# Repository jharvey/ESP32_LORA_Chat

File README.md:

# ESP32_LORA_Chat </br>
Redesign of Armachat hardware using KICAD and JLCPCB </br>
<hr />
The orginal Armachat from Peter Misenko's work at [bobricius/Armachat-circuitpython](https://github.com/bobricius/Armachat-circuitpython).</br>
This is a ESP32 with working EInk display project, which may be a useful reference https://github.com/Uspizig/EinkKeyboard</br>
 </br>
This is a redesign of bobricius/Armachat hardware to include: </br>
- ESP32 core processor </br>
- E-Ink display for lower power consumpiton </br>
- LORA communications </br>
- 18650 battery </br>
- KICAD </br>
 </br>
 
 front | back | PCB
--- | --- | ---
 |  | 
 </br>
3D model for enclosure found here </br>
https://cad.onshape.com/documents/2eca9b71ceb843e60ebed659/w/deaed59ddef0917efb45d1fe/e/0c98206fb1ddff68e078d781

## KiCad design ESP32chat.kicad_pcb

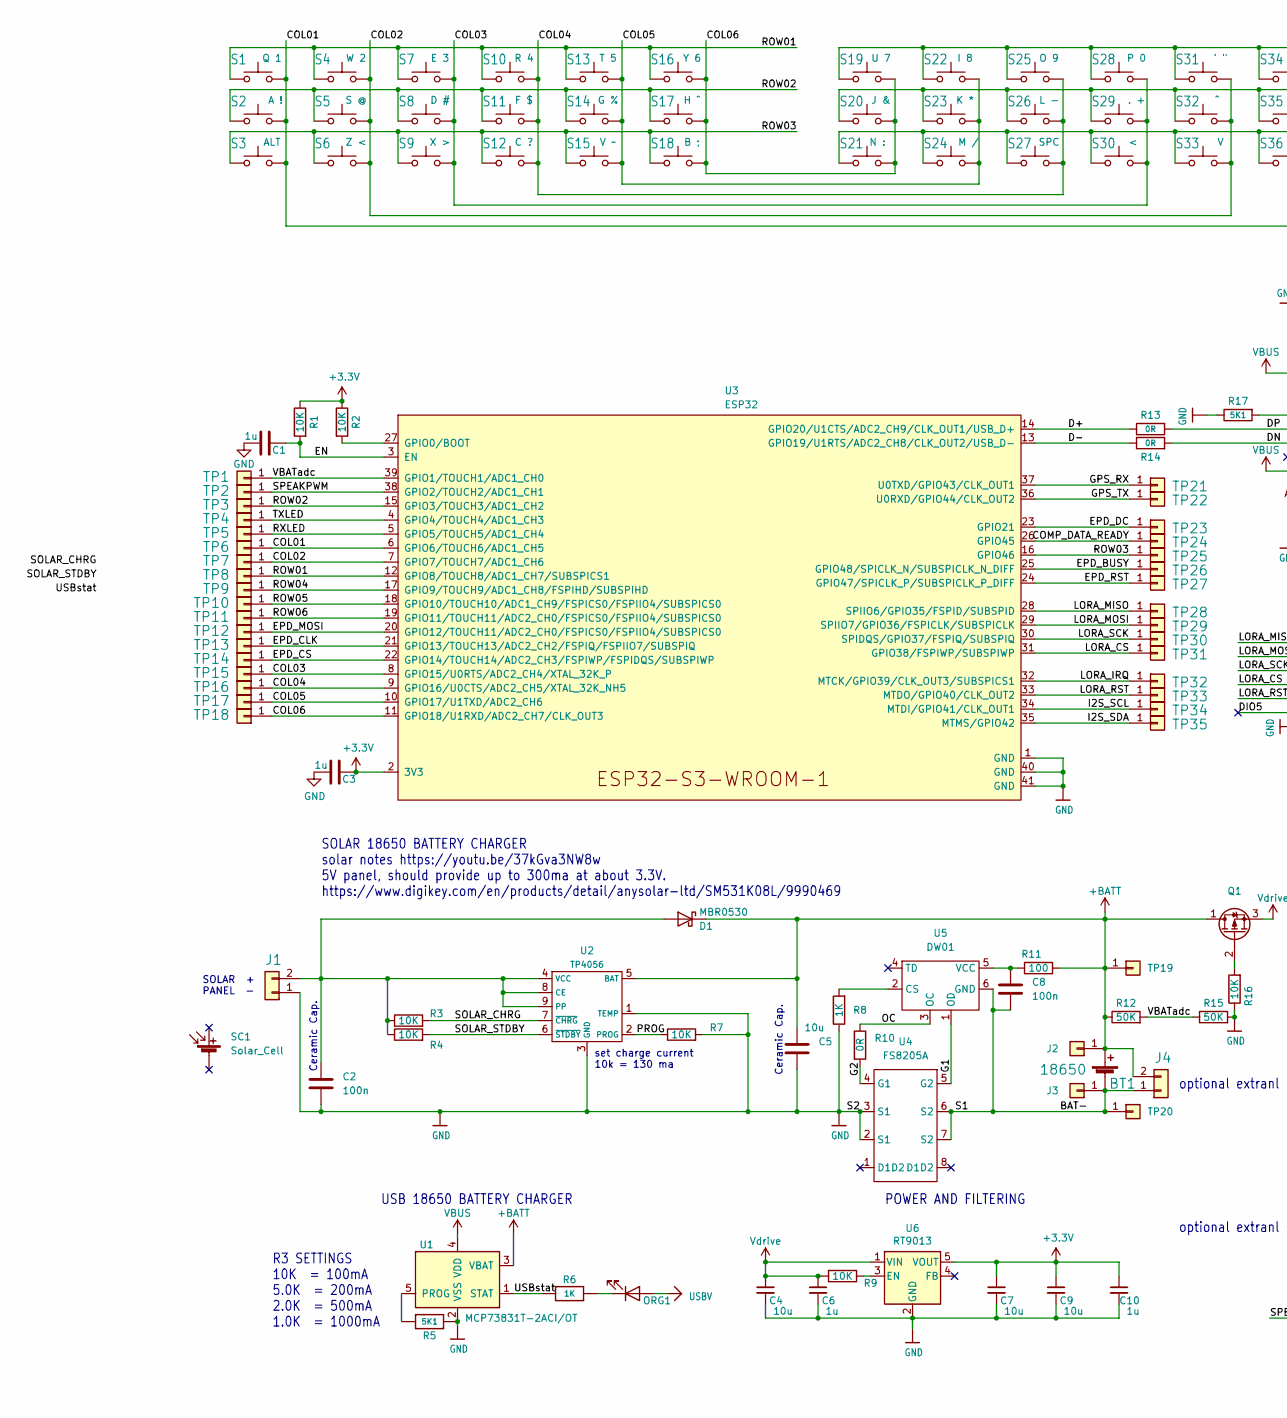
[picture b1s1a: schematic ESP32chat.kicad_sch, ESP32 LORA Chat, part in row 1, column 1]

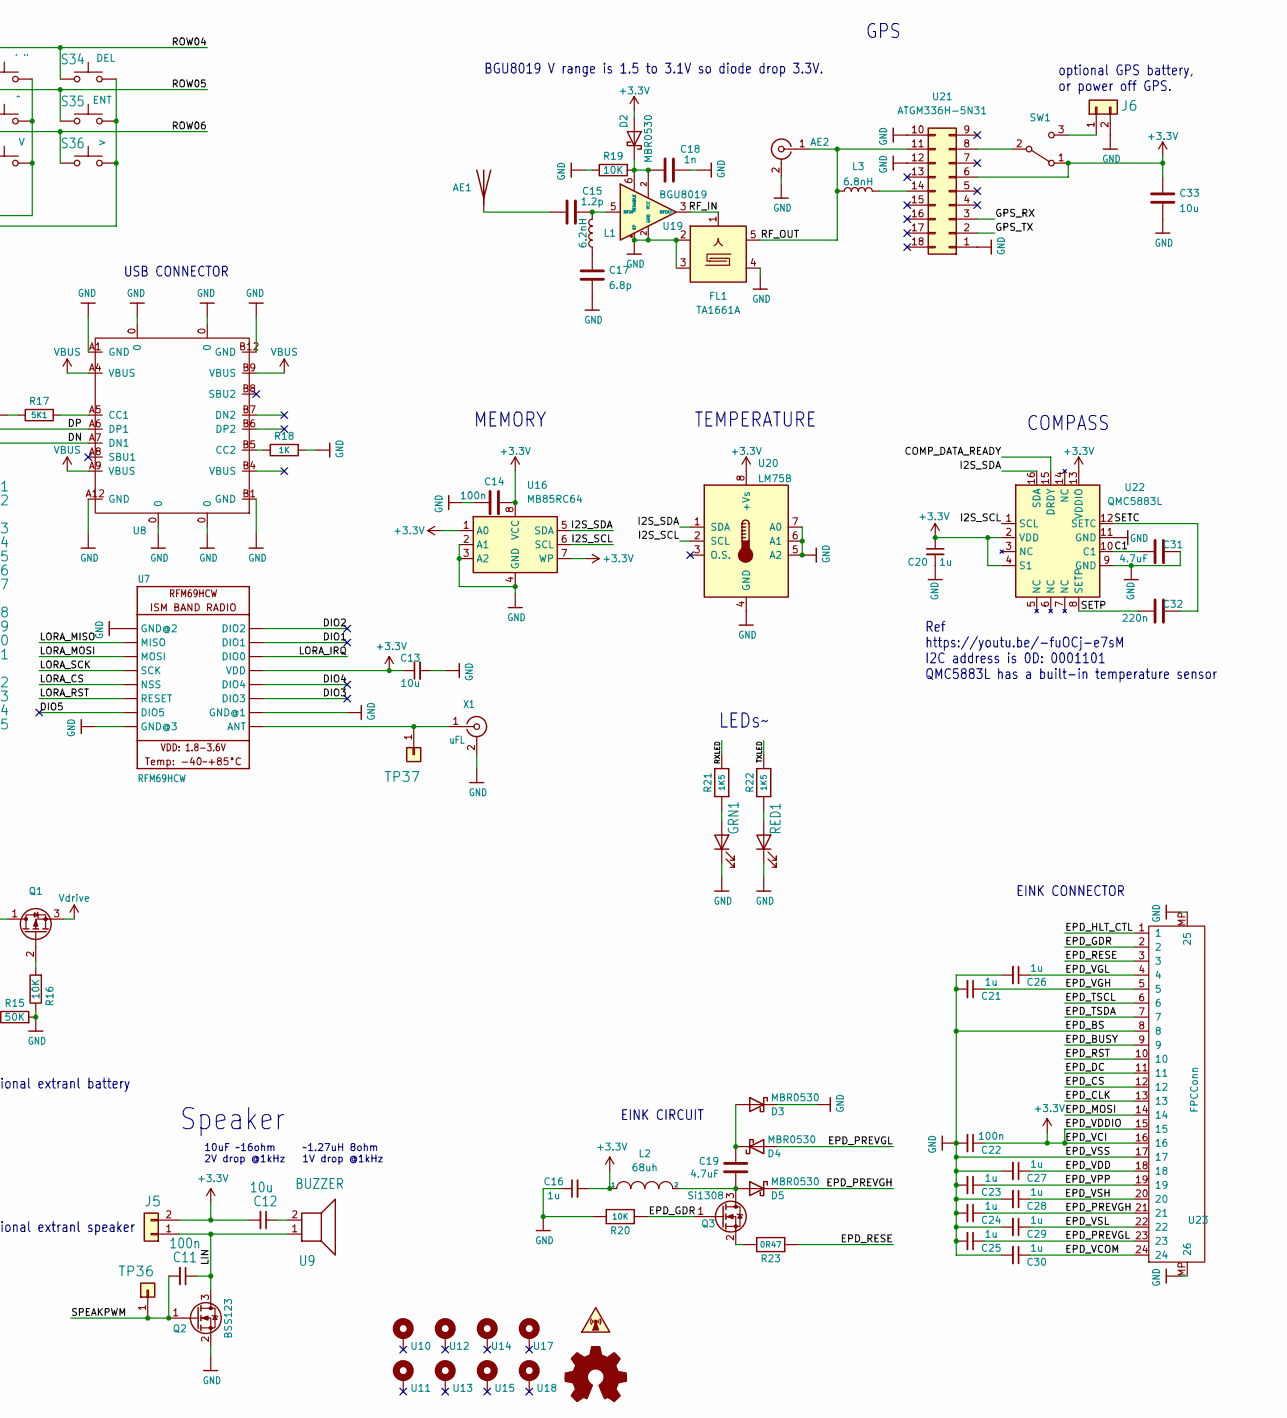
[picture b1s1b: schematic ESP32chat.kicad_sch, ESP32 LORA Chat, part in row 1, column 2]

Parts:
AE1: Antenna; KH-GPS181804-WY; LCSC C962215
AE2: Conn_Coaxial; U.FL_Hirose_U.FL-R-SMT-1_Vertical; LCSC C88374
BT1: 18650; BatteryHolder_Keystone_1042_1x18650; LCSC C2988620
C1, C3, C6, C10, C16, C20, C21, C23, C24, C25, C26, C27, C28, C29, C30: 1u; C_0603_1608Metric; LCSC C15849
C2, C8, C11, C14, C22: 100n; C_0603_1608Metric; LCSC C14663
C4, C5, C7, C9, C12, C13, C33: 10u; C_0603_1608Metric; LCSC C194427
C15: 1.2p; C_0603_1608Metric; LCSC C281768
C17: 6.8p; C_0603_1608Metric; LCSC C1679
C18: 1n; C_0603_1608Metric; LCSC C100040
C19, C31: 4.7uF; C_0603_1608Metric; LCSC C162274
C32: 220n; C_0603_1608Metric; LCSC C21120
D1, D2, D3, D4, D5: MBR0530; D_SOD-123; LCSC C77336
FL1: TA1661A; LCSC C2961690
GRN1: GRN; LED_0805_2012Metric; LCSC C434432
J1, J4, J5, J6: CONN_021X02_NO_SILK; PinHeader_1x02_P2.54mm_Vertical; LCSC DNP
J2, J3: CONN_01; SolderWirePad_1x01_SMD_5x10mm; LCSC DNP
L1: 6.2nH; L_0603_1608Metric; LCSC C98083
L2: 68uh; L_Coilcraft_XAL60xx_6.36x6.56mm; LCSC C9393
L3: 6.8nH; L_0603_1608Metric; LCSC C316305
LOGO1: SYM_Radio_Waves_Small; ESD-Logo_6.6x6mm_SilkScreen; LCSC C108781
LOGO2: OSHW-LOGOS; OSHW-Logo2_7.3x6mm_Copper; LCSC DNP
ORG1: ORG; LED_0805_2012Metric; LCSC C84262
Q1: Q_PMOS_DGS; SOT-23; LCSC C15127
Q2: BSS123; SOT-23; LCSC C79015
Q3: Si1308; SOT-323_SC-70; LCSC C469327
R1, R2, R3, R4, R7, R9, R16, R19, R20: 10K; R_0603_1608Metric; LCSC C25804
R5, R17: 5K1; R_0603_1608Metric; LCSC C23186
R6, R8, R18: 1K; R_0603_1608Metric; LCSC C21190
R10, R13, R14: 0R; R_0603_1608Metric; LCSC C21189
R11: 100; R_0603_1608Metric; LCSC C4184
R12, R15: 50K; R_0603_1608Metric; LCSC C23162
R21, R22: 1K5; R_0603_1608Metric; LCSC C22843
R23: 0R47; R_0603_1608Metric; LCSC C23411
RED1: RED; LED_0805_2012Metric; LCSC C84256
S1, S2, S3, S4, S5, S6, S7, S8, S9, S10, S11, S12, S13, S14, S15, S16, S17, S18, S19, S20, S21, S22, S23, S24, S25, S26, S27, S28, S29, S30, S31, S32, S33, S34, S35, S36: PB22; TS-1187A-C-G-B; LCSC C318886
SC1: Solar_Cell; DIGIKEY SM531K08L-ND
SW1: SW_DIP_x01; SW_SPDT_PCM12; LCSC C109335
TP1, TP2, TP3, TP4, TP5, TP6, TP7, TP8, TP9, TP10, TP11, TP12, TP13, TP14, TP15, TP16, TP17, TP18, TP19, TP20, TP21, TP22, TP23, TP24, TP25, TP26, TP27, TP28, TP29, TP30, TP31, TP32, TP33, TP34, TP35, TP36, TP37: CONN_01; TST_x01_P2.54mm_Vertical; LCSC DNP
U1: MCP73831T-2ACI/OT; SOT-23-5; LCSC C424093
U2: TP4056; SOIC-8-1EP_3.9x4.9mm_P1.27mm_EP2.29x3mm_ThermalVias; LCSC C16581
U3: ESP32; ESP32-S3-WROOM-1; LCSC C2913199
U4: FS8205A; TSSOP-8_4.4x3mm_P0.65mm; LCSC C16052
U5: DW01; SOT-23-6; LCSC C351410
U6: RT9013; SOT-23-5; LCSC C47773
U7: RFM69HCW; LCSC C2844473
U8: tp4056_KoreanHropartsElecTYPE-C-31-M-12; USB-C_SMD-TYPE-C-31-M-12; LCSC C134092
U9: BUZZER; FS-1340; LCSC C482342
U10, U11, U12, U13, U14, U15, U17, U18: MOUNTINGHOLE2.0; MountingHole_2.2mm_M2_DIN965_Pad; LCSC DNP
U16: MB85RC64; SOP-8_3.9x4.9mm_P1.27mm; LCSC C189804
U19: BGU8019; XSON6; LCSC C3190009
U20: LM75B; MSOP-8_3x3mm_P0.65mm; LCSC C2837470
U21: ATGM336H-5N31; ATGM336H-5N; LCSC C90770
U22: QMC5883L; LGA-16_3x3mm_P0.5mm; LCSC C976032
U23: FPCConn; TE_2-1734839-4_1x24-1MP_P0.5mm_Horizontal_2; LCSC C11092
X1: uFL; SMA_Molex_73251-2200_Horizontal; LCSC C411575

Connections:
+3.3V: C3.2, C7.1, C9.1, C10.1, C12.2, C13.1, C14.2, C16.2, C20.1, C22.1, C33.1, D2.2 (A), J5.2, L2.1, R1.1, R2.1, SW1.1 (A), U3.2 (3V3), U6.5 (VOUT), U7.5 (VDD), U16.1 (A0), U16.7 (WP), U16.8 (VCC), U20.8 (+Vs), U21.6, U22.2 (VDD), U22.4 (S1), U22.13 (VDDIO), U23.15, U23.16
+BATT: BT1.1 (+), C5.1, D1.1 (K), J2.1, J4.2, Q1.1 (D), R11.1, R12.1, TP19.1, U1.3 (VBAT), U2.5 (BAT)
/BAT-: BT1.2 (-), C8.2, J3.1, J4.1, TP20.1, U4.6 (S2), U4.7 (S2), U5.6 (GND)
/C1: C31.2, U22.10 (C1)
/COL01: S1.2, S2.2, S3.2, S34.2, S35.2, S36.2, TP6.1, U3.6 (GPIO6/TOUCH6/ADC1_CH5)
/COL02: S4.2, S5.2, S6.2, S31.2, S32.2, S33.2, TP7.1, U3.7 (GPIO7/TOUCH7/ADC1_CH6)
/COL03: S7.2, S8.2, S9.2, S28.2, S29.2, S30.2, TP15.1, U3.8 (GPIO15/U0RTS/ADC2_CH4/XTAL_32K_P)
/COL04: S10.2, S11.2, S12.2, S25.2, S26.2, S27.2, TP16.1, U3.9 (GPIO16/U0CTS/ADC2_CH5/XTAL_32K_NH5)
/COL05: S13.2, S14.2, S15.2, S22.2, S23.2, S24.2, TP17.1, U3.10 (GPIO17/U1TXD/ADC2_CH6)
/COL06: S16.2, S17.2, S18.2, S19.2, S20.2, S21.2, TP18.1, U3.11 (GPIO18/U1RXD/ADC2_CH7/CLK_OUT3)
/COMP_DATA_READY: TP24.1, U3.26 (GPIO45), U22.15 (DRDY)
/D+: R13.1, U3.14 (GPIO20/U1CTS/ADC2_CH9/CLK_OUT1/USB_D+)
/D-: R14.1, U3.13 (GPIO19/U1RTS/ADC2_CH8/CLK_OUT2/USB_D-)
/DIO1: U7.7 (DIO1)
/DIO2: U7.8 (DIO2)
/DIO3: U7.3 (DIO3)
/DIO4: U7.4 (DIO4)
/DIO5: U7.15 (DIO5)
/DN: R14.2, U8.A7 (DN1)
/DP: R13.2, U8.A6 (DP1)
/EN: C1.2, R1.2, U3.3 (EN)
/EPD_BUSY: TP26.1, U3.25 (GPIO48/SPICLK_N/SUBSPICLK_N_DIFF), U23.9
/EPD_CLK: TP13.1, U3.21 (GPIO13/TOUCH13/ADC2_CH2/FSPIQ/FSPIIO7/S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), U23.13
/EPD_CS: TP14.1, U3.22 (GPIO14/TOUCH14/ADC2_CH3/FSPIWP/FSPIDQS/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), U23.12
/EPD_DC: TP23.1, U3.23 (GPIO21), U23.11
/EPD_GDR: Q3.1 (G), R20.1, U23.2
/EPD_HLT_CTL: U23.1
/EPD_MOSI: TP12.1, U3.20 (GPIO12/TOUCH11/ADC2_CH0/FSPICS0/FSPIIO4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), U23.14
/EPD_PREVGH: C24.1, D5.1 (K), U23.21
/EPD_PREVGL: C25.1, D4.2 (A), U23.23
/EPD_RESE: R23.1, U23.3
/EPD_RST: TP27.1, U3.24 (GPIO47/SPICLK_P/SUBSPICLK_P_DIFF), U23.10
/EPD_TSCL: U23.6
/EPD_TSDA: U23.7
/EPD_VCOM: C30.1, U23.24
/EPD_VDD: C27.1, U23.18
/EPD_VGH: C21.1, U23.5
/EPD_VGL: C26.1, U23.4
/EPD_VPP: C23.1, U23.19
/EPD_VSH: C28.1, U23.20
/EPD_VSL: C29.1, U23.22
/G1: U4.5 (G2), U5.1 (OD)
/G2: R10.2, U4.4 (G1)
/GPS_RX: TP21.1, U3.37 (U0TXD/GPIO43/CLK_OUT1), U21.3
/GPS_TX: TP22.1, U3.36 (U0RXD/GPIO44/CLK_OUT2), U21.2
/I2S_SCL: TP34.1, U3.34 (MTDI/GPIO41/CLK_OUT1), U16.6 (SCL), U20.2 (SCL), U22.1 (SCL)
/I2S_SDA: TP35.1, U3.35 (MTMS/GPIO42), U16.5 (SDA), U20.1 (SDA), U22.16 (SDA)
/LIN: C11.1, J5.1, Q2.3 (D), U9.1
/LORA_CS: TP31.1, U3.31 (GPIO38/FSPIWP/SUBSPIWP), U7.13 (NSS)
/LORA_IRQ: TP32.1, U3.32 (MTCK/GPIO39/CLK_OUT3/SUBSPICS1), U7.6 (DIO0)
/LORA_MISO: TP28.1, U3.28 (SPIIO6/GPIO35/FSPID/SUBSPID), U7.10 (MISO)
/LORA_MOSI: TP29.1, U3.29 (SPIIO7/GPIO36/FSPICLK/SUBSPICLK), U7.11 (MOSI)
/LORA_RST: TP33.1, U3.33 (MTDO/GPIO40/CLK_OUT2), U7.14 (RESET)
/LORA_SCK: TP30.1, U3.30 (SPIDQS/GPIO37/FSPIQ/SUBSPIQ), U7.12 (SCK)
/OC: R10.1, U5.3 (OC)
/PROG: R7.1, U2.2 (PROG)
/RF_IN: FL1.1, U19.3 (RFOUT)
/RF_OUT: AE2.1 (In), FL1.5, L3.1, U21.11
/ROW01: S1.1, S4.1, S7.1, S10.1, S13.1, S16.1, TP8.1, U3.12 (GPIO8/TOUCH8/ADC1_CH7/SUBSPICS1)
/ROW02: S2.1, S5.1, S8.1, S11.1, S14.1, S17.1, TP3.1, U3.15 (GPIO3/TOUCH3/ADC1_CH2)
/ROW03: S3.1, S6.1, S9.1, S12.1, S15.1, S18.1, TP25.1, U3.16 (GPIO46)
/ROW04: S19.1, S22.1, S25.1, S28.1, S31.1, S34.1, TP9.1, U3.17 (GPIO9/TOUCH9/ADC1_CH8/FSPIHD/SUBSPIHD)
/ROW05: S20.1, S23.1, S26.1, S29.1, S32.1, S35.1, TP10.1, U3.18 (GPIO10/TOUCH10/ADC1_CH9/FSPICS0/FSPIIO4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)
/ROW06: S21.1, S24.1, S27.1, S30.1, S33.1, S36.1, TP11.1, U3.19 (GPIO11/TOUCH11/ADC2_CH0/FSPICS0/FSPIIO4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)
/RXLED: R21.1, TP5.1, U3.5 (GPIO5/TOUCH5/ADC1_CH4)
/SETC: C32.1, U22.12 (SETC)
/SETP: C32.2, U22.8 (SETP)
/SOLAR_CHRG: R3.2, U2.7 (~CHRG)
/SOLAR_STDBY: R4.2, U2.6 (~STDBY)
/SPEAKPWM: C11.2, Q2.1 (G), TP2.1, TP36.1, U3.38 (GPIO2/TOUCH2/ADC1_CH1)
/TXLED: R22.1, TP4.1, U3.4 (GPIO4/TOUCH4/ADC1_CH3)
/USBstat: R6.2, U1.1 (STAT)
/VBATadc: R12.2, R15.1, TP1.1, U3.39 (GPIO1/TOUCH1/ADC1_CH0)
unnamed: AE1.1 (A), C15.1
unnamed: C2.1, D1.2 (A), J1.2, R3.1, R4.1, U2.4 (VCC), U2.8 (CE), U2.9 (PP)
unnamed: C8.1, R11.2, U5.5 (VCC)
unnamed: C12.1, U9.2
unnamed: C15.2, L1.2, U19.5 (RFIN)
unnamed: C17.1, L1.1
unnamed: C19.1, D5.2 (A), L2.2, Q3.3 (D)
unnamed: C19.2, D3.2 (A), D4.1 (K)
unnamed: GRN1.2 (A), R21.2
unnamed: J6.1, SW1.3 (C)
unnamed: L3.2, U21.14
unnamed: ORG1.1 (K), R6.1
unnamed: Q1.2 (G), R16.2
unnamed: Q3.2 (S), R23.2
unnamed: R2.2, U3.27 (GPIO0/BOOT)
unnamed: R5.2, U1.5 (PROG)
unnamed: R8.2, U5.2 (CS)
unnamed: R9.1, U6.3 (EN)
unnamed: R17.2, U8.A5 (CC1)
unnamed: R18.1, U8.B5 (CC2)
unnamed: R22.2, RED1.2 (A)
unnamed: SW1.2 (B), U21.8
unnamed: TP37.1, U7.1 (ANT), X1.1 (In)
Vdrive: C4.1, C6.1, Q1.3 (S), R9.2, U6.1 (VIN)

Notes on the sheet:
Speaker
LEDs~~{}
BGU8019 V range is 1.5 to 3.1V so diode drop 3.3V.
COMPASS
EINK CIRCUIT
Ceramic Cap.
EINK CONNECTOR
set charge current 10k = 130 ma
optional GPS battery, or power off GPS.
~1.27uH 8ohm 1V drop @1kHz
Ref https://youtu.be/-fuOCj-e7sM I2C address is 0D: 0001101 QMC5883L has a built-in temperature sensor
10uF ~16ohm 2V drop @1kHz
GPS
USB CONNECTOR
TEMPERATURE
R3 SETTINGS 10K = 100mA 5.0K = 200mA 2.0K = 500mA 1.0K = 1000mA
MEMORY
optional extranl battery
POWER AND FILTERING
SOLAR 18650 BATTERY CHARGER solar notes https://youtu.be/37kGva3NW8w 5V panel, should provide up to 300ma at about 3.3V. https://www.digikey.com/en/products/detail/anysolar-ltd/SM531K08L/9990469
SOLAR + PANEL -
optional extranl speaker
USB 18650 BATTERY CHARGER

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
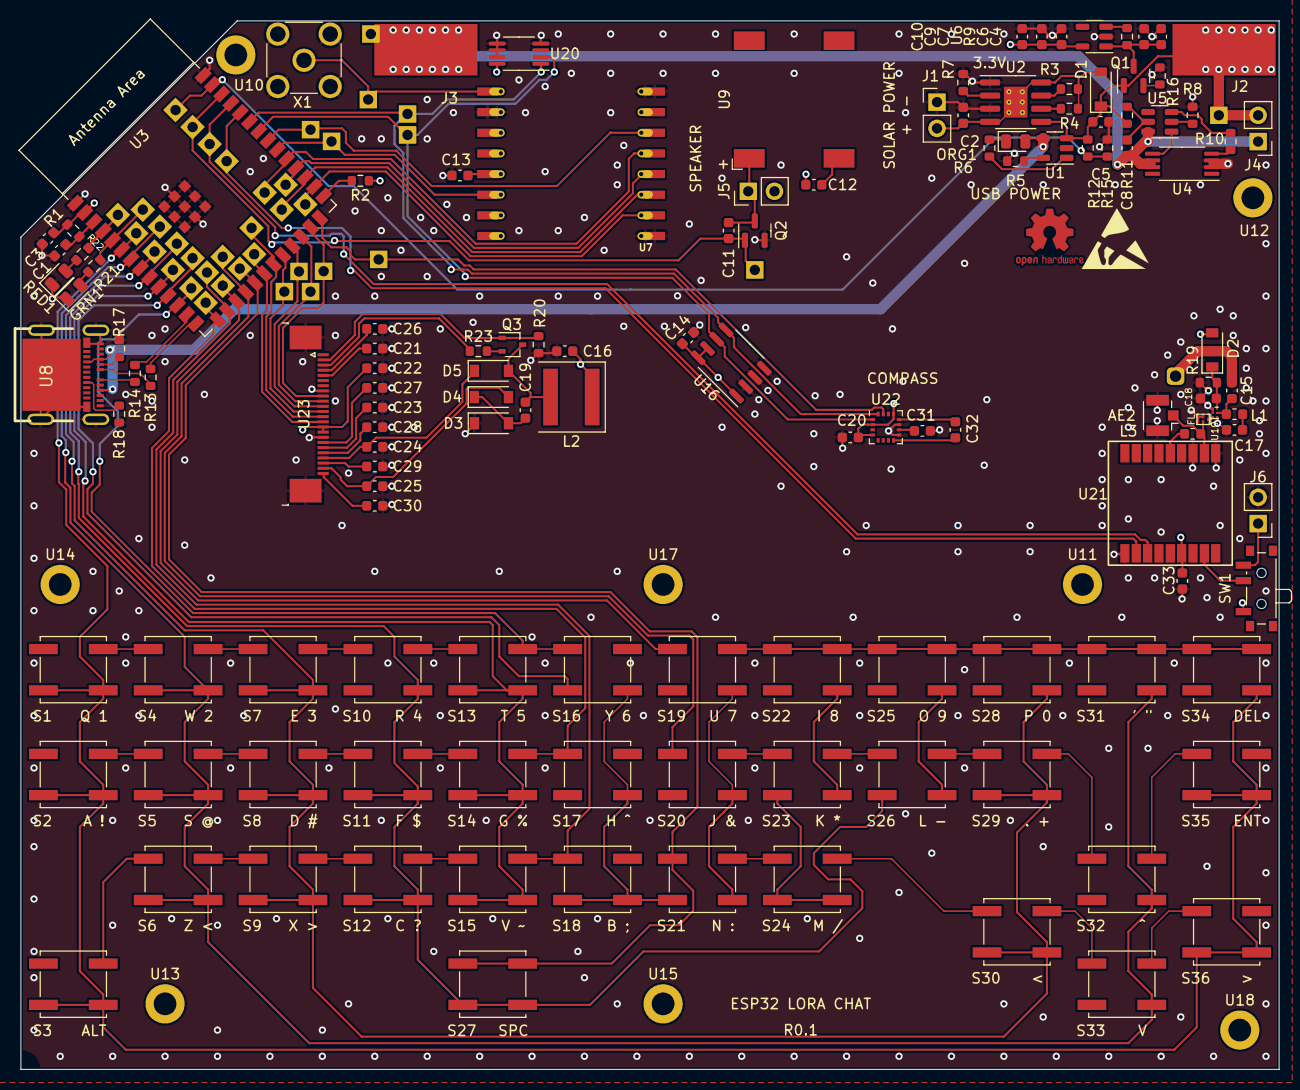
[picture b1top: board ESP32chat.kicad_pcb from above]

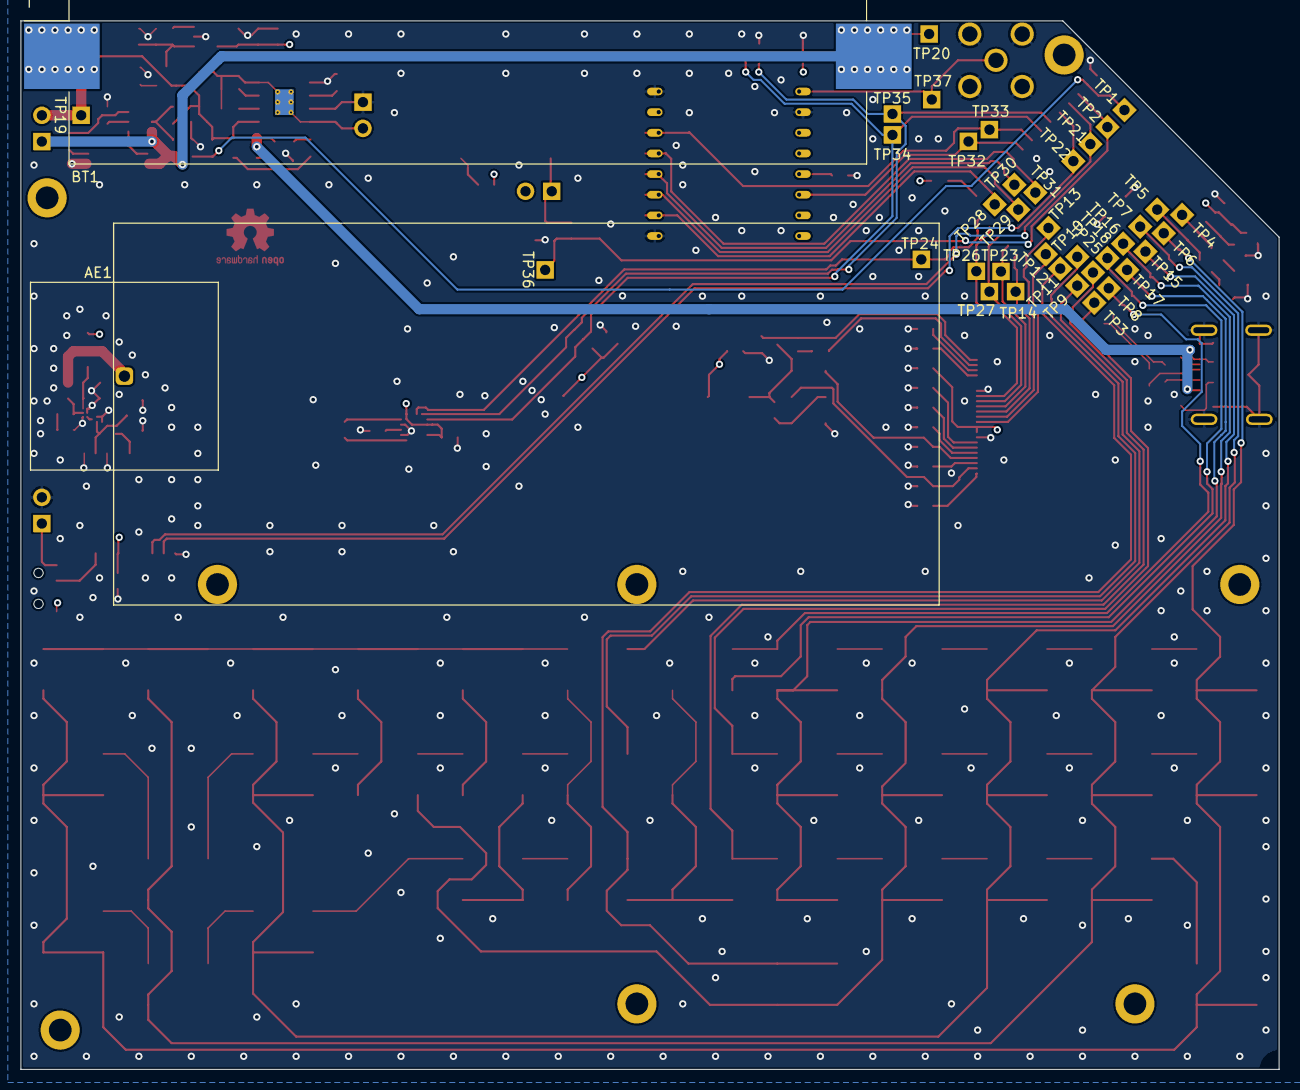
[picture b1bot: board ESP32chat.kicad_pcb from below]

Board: 4 copper layers, 121.9 x 101.6 mm, 180 parts (39 on the bottom side), 92 nets.

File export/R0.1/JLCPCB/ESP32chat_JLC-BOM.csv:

Comment,Designator,Footprint,LCSC
"Antenna","AE1","KICAD_Footprints:KH-GPS181804-WY","C962215"
"Conn_Coaxial","AE2","Connector_Coaxial:U.FL_Hirose_U.FL-R-SMT-1_Vertical","C88374"
"18650","BT1","Battery:BatteryHolder_Keystone_1042_1x18650","C2988620"
"1u","C1,C3,C6,C10,C16,C20,C21,C23,C24,C25,C26,C27,C28,C29,C30","Capacitor_SMD:C_0603_1608Metric","C15849"
"1.2p","C15","Capacitor_SMD:C_0603_1608Metric","C281768"
"6.8p","C17","Capacitor_SMD:C_0603_1608Metric","C1679"
"1n","C18","Capacitor_SMD:C_0603_1608Metric","C100040"
"4.7uF","C19,C31","Capacitor_SMD:C_0603_1608Metric","C162274"
"100n","C2,C8,C11,C14,C22","Capacitor_SMD:C_0603_1608Metric","C14663"
"220n","C32","Capacitor_SMD:C_0603_1608Metric","C21120"
"10u","C4,C5,C7,C9,C12,C13,C33","Capacitor_SMD:C_0603_1608Metric","C194427"
"MBR0530","D1,D2,D3,D4,D5","Diode_SMD:D_SOD-123","C77336"
"TA1661A","FL1","KICAD_Footprints:TA1661A","C2961690"
"GRN","GRN1","LED_SMD:LED_0805_2012Metric","C434432"
"CONN_021X02_NO_SILK","J1,J4,J5,J6","Connector_PinHeader_2.54mm:PinHeader_1x02_P2.54mm_Vertical","DNP"
"CONN_01","J2,J3","Connector_Wire:SolderWirePad_1x01_SMD_5x10mm","DNP"
"6.2nH","L1","Inductor_SMD:L_0603_1608Metric","C98083"
"68uh","L2","Inductor_SMD:L_Coilcraft_XAL60xx_6.36x6.56mm","C9393"
"6.8nH","L3","Inductor_SMD:L_0603_1608Metric","C316305"
"SYM_Radio_Waves_Small","LOGO1","Symbol:ESD-Logo_6.6x6mm_SilkScreen","C108781"
"OSHW-LOGOS","LOGO2","Symbol:OSHW-Logo2_7.3x6mm_Copper","DNP"
"ORG","ORG1","LED_SMD:LED_0805_2012Metric","C84262"
"Q_PMOS_DGS","Q1","Package_TO_SOT_SMD:SOT-23","C15127"
"BSS123","Q2","Package_TO_SOT_SMD:SOT-23","C79015"
"Si1308","Q3","Package_TO_SOT_SMD:SOT-323_SC-70","C469327"
"10K","R1,R2,R3,R4,R7,R9,R16,R19,R20","Resistor_SMD:R_0603_1608Metric","C25804"
"0R","R10,R13,R14","Resistor_SMD:R_0603_1608Metric","C21189"
"100","R11","Resistor_SMD:R_0603_1608Metric","C4184"
"50K","R12,R15","Resistor_SMD:R_0603_1608Metric","C23162"
"1K5","R21,R22","Resistor_SMD:R_0603_1608Metric","C22843"
"0R47","R23","Resistor_SMD:R_0603_1608Metric","C23411"
"5K1","R5,R17","Resistor_SMD:R_0603_1608Metric","C23186"
"1K","R6,R8,R18","Resistor_SMD:R_0603_1608Metric","C21190"
"RED","RED1","LED_SMD:LED_0805_2012Metric","C84256"
"PB22","S1,S2,S3,S4,S5,S6,S7,S8,S9,S10,S11,S12,S13,S14,S15,S16,S17,S18,S19,S20,S21,S22,S23,S24,S25,S26,S27,S28,S29,S30,S31,S32,S33,S34,S35,S36","KICAD_Footprints:TS-1187A-C-G-B","C318886"
"Solar_Cell","SC1","","DNP"
"SW_DIP_x01","SW1","Button_Switch_SMD:SW_SPDT_PCM12","C109335"
"CONN_01","TP1,TP2,TP3,TP4,TP5,TP6,TP7,TP8,TP9,TP10,TP11,TP12,TP13,TP14,TP15,TP16,TP17,TP18,TP19,TP20,TP21,TP22,TP23,TP24,TP25,TP26,TP27,TP28,TP29,TP30,TP31,TP32,TP33,TP34,TP35,TP36,TP37","KICAD_Footprints:TST_x01_P2.54mm_Vertical","DNP"
"MCP73831T-2ACI/OT","U1","Package_TO_SOT_SMD:SOT-23-5","C424093"
"MOUNTINGHOLE2.0","U10,U11,U12,U13,U14,U15,U17,U18","MountingHole:MountingHole_2.2mm_M2_DIN965_Pad","DNP"
"MB85RC64","U16","Package_SO:SOP-8_3.9x4.9mm_P1.27mm","C189804"
"BGU8019 ","U19","KICAD_Footprints:XSON6","C3190009"
"TP4056","U2","Package_SO:SOIC-8-1EP_3.9x4.9mm_P1.27mm_EP2.29x3mm_ThermalVias","C16581"
"LM75B","U20","Package_SO:MSOP-8_3x3mm_P0.65mm","C2837470"
"ATGM336H-5N31","U21","KICAD_Footprints:ATGM336H-5N","C90770"
"QMC5883L","U22","Package_LGA:LGA-16_3x3mm_P0.5mm","C976032"
"FPCConn","U23","KICAD_Footprints:TE_2-1734839-4_1x24-1MP_P0.5mm_Horizontal_2","C11092"
"ESP32","U3","KICAD_Footprints:ESP32-S3-WROOM-1","C2913199"
"FS8205A","U4","Package_TO_SOT_SMD:SOT-23-6","C16052"
"DW01","U5","Package_TO_SOT_SMD:SOT-23-6","C351410"
"RT9013","U6","Package_TO_SOT_SMD:SOT-23-5","C47773"
"RFM69HCW","U7","KICAD_Footprints:RFM69HCW","C2844473"
"tp4056_KoreanHropartsElecTYPE-C-31-M-12","U8","KICAD_Footprints:USB-C_SMD-TYPE-C-31-M-12","C134092"
"BUZZER","U9","KICAD_Footprints:FS-1340","C482342"
"uFL","X1","Connector_Coaxial:SMA_Molex_73251-2200_Horizontal","C411575"

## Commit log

2022-11-22 DRAFT initial check in, still needs lots of work.
2022-11-23 DRAFT Still needs silk screen, would be nice to remove errors.
2022-11-23 Almost ready for review.
2022-11-24 Added 3D files for a 3D printed enclosure.
2022-11-24 Update README.md
    Added ISO images
2022-11-24 Update README.md
    Added link to a working EInk / ESP32 reference design.
2022-11-24 Added PCB ISO graphic
2022-11-24 Update README.md
    Formatting, and added link to 3D model for enclosure.
2022-11-25 Added license file
2022-11-25 DRAFT added solar charging circuit, changed to 6X6 key scanning, 36 buttons with less consumed GPIO. Added temperature sensor to monitor the battery. Added GPS module.
2022-11-26 renamed symbol file
2022-11-27 DRAFT laying down copper now, many traces still need to be installed. Checked in for archival purposes.
2022-11-27 DRAFT Almost ready for review again. Checking in for archival purposes.
2022-11-27 Ready for review.
2022-11-28 Some corrections to align with JLCPCB verification, added I2C memory chip.
2022-11-28 Updated pictures
2022-11-28 updated images
    updated images for 2nd draft of the layout.
2022-11-28 Updated kepad layout
2022-11-28 added battery cover, updated 3D models for 3D printed enclosure.
2022-11-28 Updated images to show current design changes.
2022-12-04 Added SD memory, Added 2nd USB for 232 initial circuit python programming
2022-12-04 updated the 3D enclosure to accommodate the extra USB port.
2022-12-05 Updated BOM
